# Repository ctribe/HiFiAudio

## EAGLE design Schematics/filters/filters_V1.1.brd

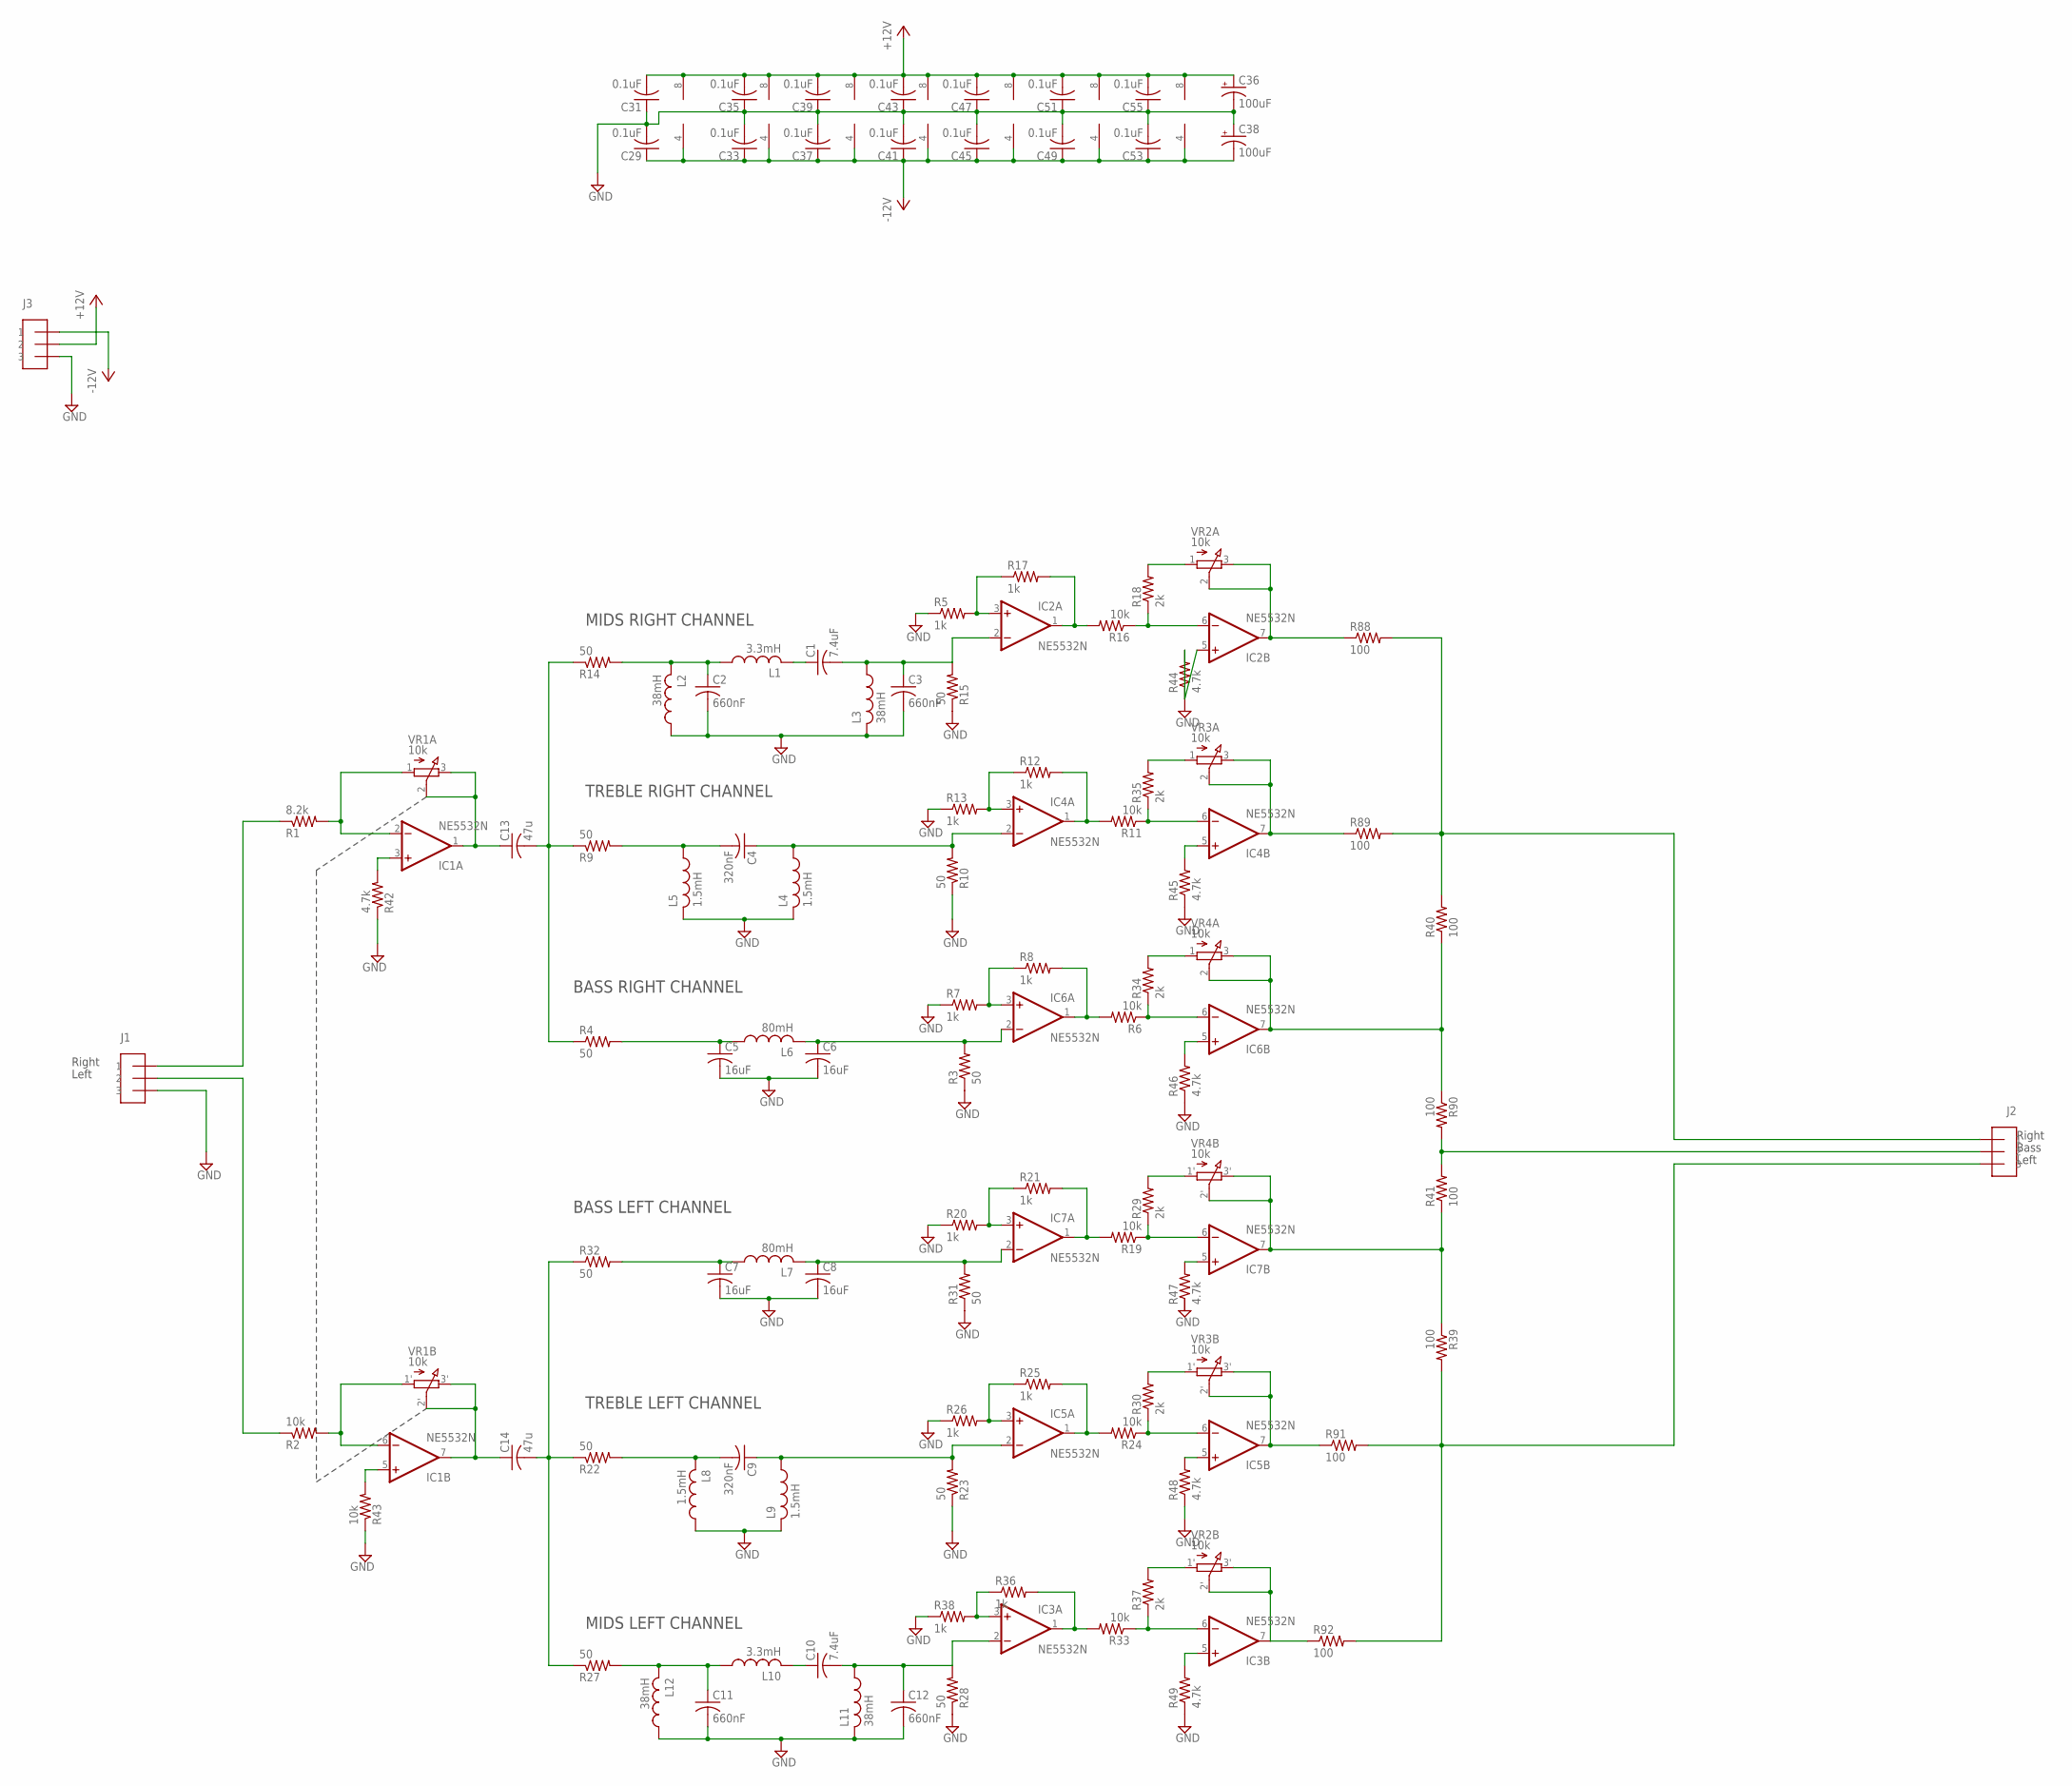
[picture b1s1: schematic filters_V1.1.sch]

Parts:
C1, C10: 7.4uF; C050-024X044
C2, C3, C11, C12: 660nF; C050-024X044
C4, C9: 320nF; C050-024X044
C5, C6, C7, C8: 16uF; C050-024X044
C13, C14: 47u; C050-024X044
C29, C31, C33, C35, C37, C39, C41, C43, C45, C47, C49, C51, C53, C55: 0.1uF; C050-024X044
C36, C38: 100uF; E2,5-6
IC1, IC2, IC3, IC4, IC5, IC6, IC7: NE5532N; DIL08
J1, J2, J3: 3_PIN_AMPCONN
L1, L10: 3.3mH; 6000-XXXX-RC
L2, L3, L11, L12: 38mH; 6000-XXXX-RC
L4, L5, L8, L9: 1.5mH; 6000-XXXX-RC
L6, L7: 80mH; 6000-XXXX-RC
R1: 8.2k; 0204V
R2, R6, R11, R16, R19, R24, R33, R43: 10k; 0204V
R3, R4, R9, R10, R14, R15, R22, R23, R27, R28, R31, R32: 50; 0204V
R5, R7, R8, R12, R13, R17, R20, R21, R25, R26, R36, R38: 1k; 0204V
R18, R29, R30, R34, R35, R37: 2k; 0204V
R39, R40, R41, R88, R89, R90, R91, R92: 100; 0204V
R42, R44, R45, R46, R47, R48, R49: 4.7k; 0204V
VR1: 10k; VOL_POT_2GANG
VR2, VR3, VR4: 10k; TONE_POT_2GANG

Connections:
+12V: C31.2, C35.2, C36.+, C39.2, C43.2, C47.2, C51.2, C55.2, IC1.8 (V+), IC2.8 (V+), IC3.8 (V+), IC4.8 (V+), IC5.8 (V+), IC6.8 (V+), IC7.8 (V+), J3.2
-12V: C29.1, C33.1, C37.1, C38.-, C41.1, C45.1, C49.1, C53.1, IC1.4 (V-), IC2.4 (V-), IC3.4 (V-), IC4.4 (V-), IC5.4 (V-), IC6.4 (V-), IC7.4 (V-), J3.1
GND: C2.2, C3.2, C5.2, C6.2, C7.2, C8.2, C11.2, C12.2, C29.2, C31.1, C33.2, C35.1, C36.-, C37.2, C38.+, C39.1, C41.2, C43.1, C45.2, C47.1, C49.2, C51.1, C53.2, C55.1, J1.3, J3.3, L2.1, L3.2, L4.2, L5.2, L8.1, L9.2, L11.2, L12.1, R3.1, R5.1, R7.1, R10.1, R13.1, R15.1, R20.1, R23.1, R26.1, R28.1, R31.1, R38.1, R42.1, R43.1, R44.2, R45.1, R46.1, R48.1, R49.1
MVO: IC6.7 (OUT), R40.1, R90.1, VR4.2 (1_2), VR4.3 (1_3)
unnamed: IC1.2 (-IN), R1.2, VR1.1
unnamed: C13.1, IC1.1 (OUT), VR1.2, VR1.3
unnamed: IC1.6 (-IN), R2.2, VR1.1' (1)
unnamed: IC2.6 (-IN), R16.1, R18.1
unnamed: C14.1, IC1.7 (OUT), VR1.2' (2), VR1.3' (3)
unnamed: IC6.3 (+IN), R7.2, R8.1
unnamed: C6.1, IC6.2 (-IN), L6.2, R3.2
unnamed: IC3.6 (-IN), R33.1, R37.1
unnamed: IC4.3 (+IN), R12.1, R13.2
unnamed: J2.1, R40.2, R88.2, R89.2
unnamed: IC6.6 (-IN), R6.1, R34.1
unnamed: C5.1, L6.1, R4.2
unnamed: C4.2, L5.1, R9.2
unnamed: C8.1, IC7.2 (-IN), L7.2, R31.2
unnamed: IC2.1 (OUT), R16.2, R17.2
unnamed: IC1.3 (+IN), R42.2
unnamed: IC4.1 (OUT), R11.2, R12.2
unnamed: IC4.6 (-IN), R11.1, R35.1
unnamed: J2.2, R41.2, R90.2
unnamed: IC1.5 (+IN), R43.2
unnamed: IC2.7 (OUT), R88.1, VR2.2 (1_2), VR2.3 (1_3)
unnamed: C13.2, R4.1, R9.1, R14.1
unnamed: C2.1, L1.1, L2.2, R14.2
unnamed: R18.2, VR2.1 (1_1)
unnamed: IC7.6 (-IN), R19.1, R29.1
unnamed: J1.1, R1.1
unnamed: IC2.3 (+IN), R5.2, R17.1
unnamed: IC2.5 (+IN), R44.1
unnamed: C1.1, L1.2
unnamed: C9.2, L8.2, R22.2
unnamed: IC5.5 (+IN), R48.2
unnamed: IC5.1 (OUT), R24.2, R25.2
unnamed: IC5.6 (-IN), R24.1, R30.1
unnamed: C11.1, L10.1, L12.2, R27.2
unnamed: C10.1, L10.2
unnamed: IC4.5 (+IN), R45.2
unnamed: R29.2, VR4.1' (1_1)
unnamed: J2.3, R39.2, R91.2, R92.2
unnamed: IC6.5 (+IN), R46.2
unnamed: IC7.7 (OUT), R39.1, R41.1, VR4.2' (1_2), VR4.3' (1_3)
unnamed: IC5.7 (OUT), R91.1, VR3.2' (1_2), VR3.3' (1_3)
unnamed: R30.2, VR3.1' (1_1)
unnamed: IC7.1 (OUT), R19.2, R21.2
unnamed: C7.1, L7.1, R32.2
unnamed: IC7.3 (+IN), R20.2, R21.1
unnamed: IC5.3 (+IN), R25.1, R26.2
unnamed: IC3.1 (OUT), R33.2, R36.2
unnamed: IC3.5 (+IN), R49.2
unnamed: IC7.5 (+IN), R47.2
unnamed: IC3.7 (OUT), R92.1, VR2.2' (1_2), VR2.3' (1_3)
unnamed: R34.2, VR4.1 (1_1)
unnamed: IC4.7 (OUT), R89.1, VR3.2 (1_2), VR3.3 (1_3)
unnamed: R35.2, VR3.1 (1_1)
unnamed: R37.2, VR2.1' (1_1)
unnamed: IC3.3 (+IN), R36.1, R38.2
unnamed: C10.2, C12.1, IC3.2 (-IN), L11.1, R28.2
unnamed: C14.2, R22.1, R27.1, R32.1
unnamed: C9.1, IC5.2 (-IN), L9.1, R23.2
unnamed: C4.1, IC4.2 (-IN), L4.1, R10.2
unnamed: IC6.1 (OUT), R6.2, R8.2
unnamed: C1.2, C3.1, IC2.2 (-IN), L3.1, R15.2
unnamed: J1.2, R2.1

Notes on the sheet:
BASS RIGHT CHANNEL
TREBLE RIGHT CHANNEL
MIDS RIGHT CHANNEL
BASS LEFT CHANNEL
TREBLE LEFT CHANNEL
MIDS LEFT CHANNEL
Left
Right
Bass

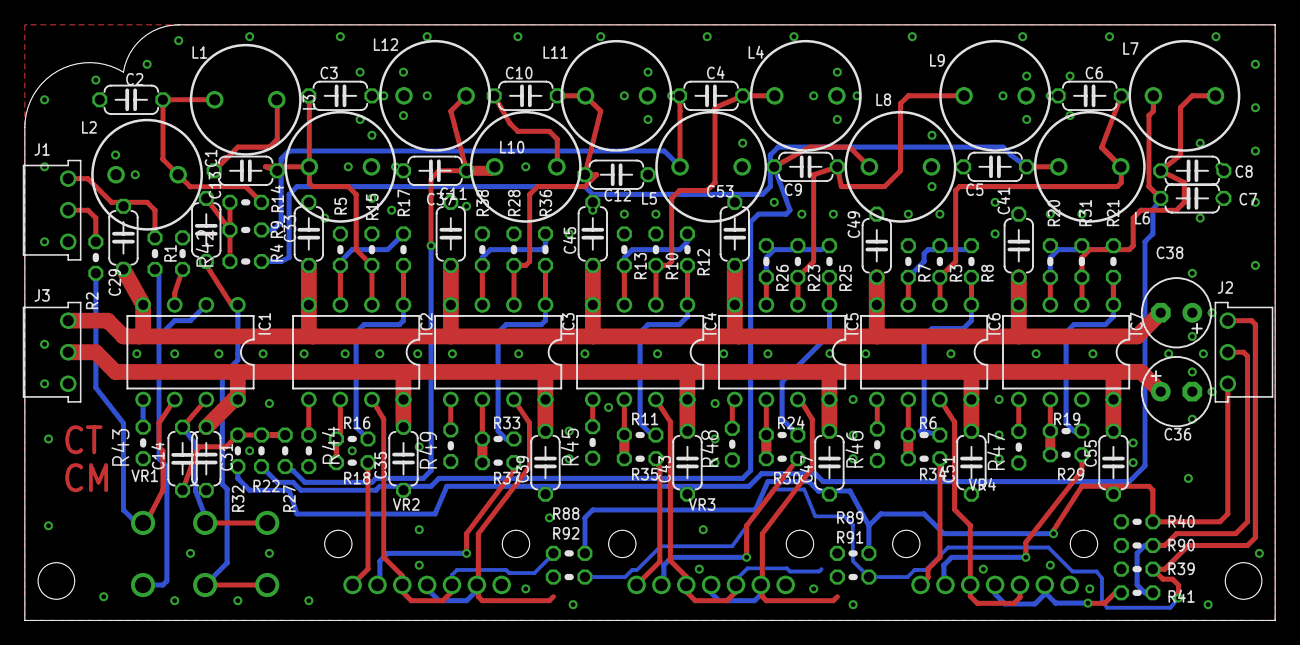
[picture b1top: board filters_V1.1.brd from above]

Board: 2 copper layers, 100.6 x 47.9 mm, 110 parts (0 on the bottom side), 66 nets.
